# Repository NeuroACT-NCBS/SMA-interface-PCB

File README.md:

# SMA Interface PCB

KiCad PCB design for a reward-well controller for behavioral neuroscience experiments.

## Function

Built around an **RP2040-Zero** microcontroller. Takes 6 SMA coaxial sensor inputs from the spikegadgets ECU, through a schmitt-trigger buffer, and drives 4 TMC2209 stepper motors for reward dispensing. 8× AO3400A MOSFETs switch light and sounds. Two stacked USB-A ports allow to connect with the reward wells.

## Requirements

- [KiCad](https://www.kicad.org/) 10.0+

Clone with `--recurse-submodules` to pull the [NeuroACT-KiCad-libraries](https://github.com/NeuroACT-NCBS/NeuroACT-KiCad-libraries) automatically:

```bash
git clone --recurse-submodules https://github.com/NeuroACT-NCBS/SMA-interface-pcb.git
```

## KiCad Plugins

- **Fabrication Toolkit** — for generating production Gerber files
- **Round Tracks** — configured via `.round-tracks-config`

## License

CERN Open Hardware Licence Version 2 — see [LICENSE](LICENSE)

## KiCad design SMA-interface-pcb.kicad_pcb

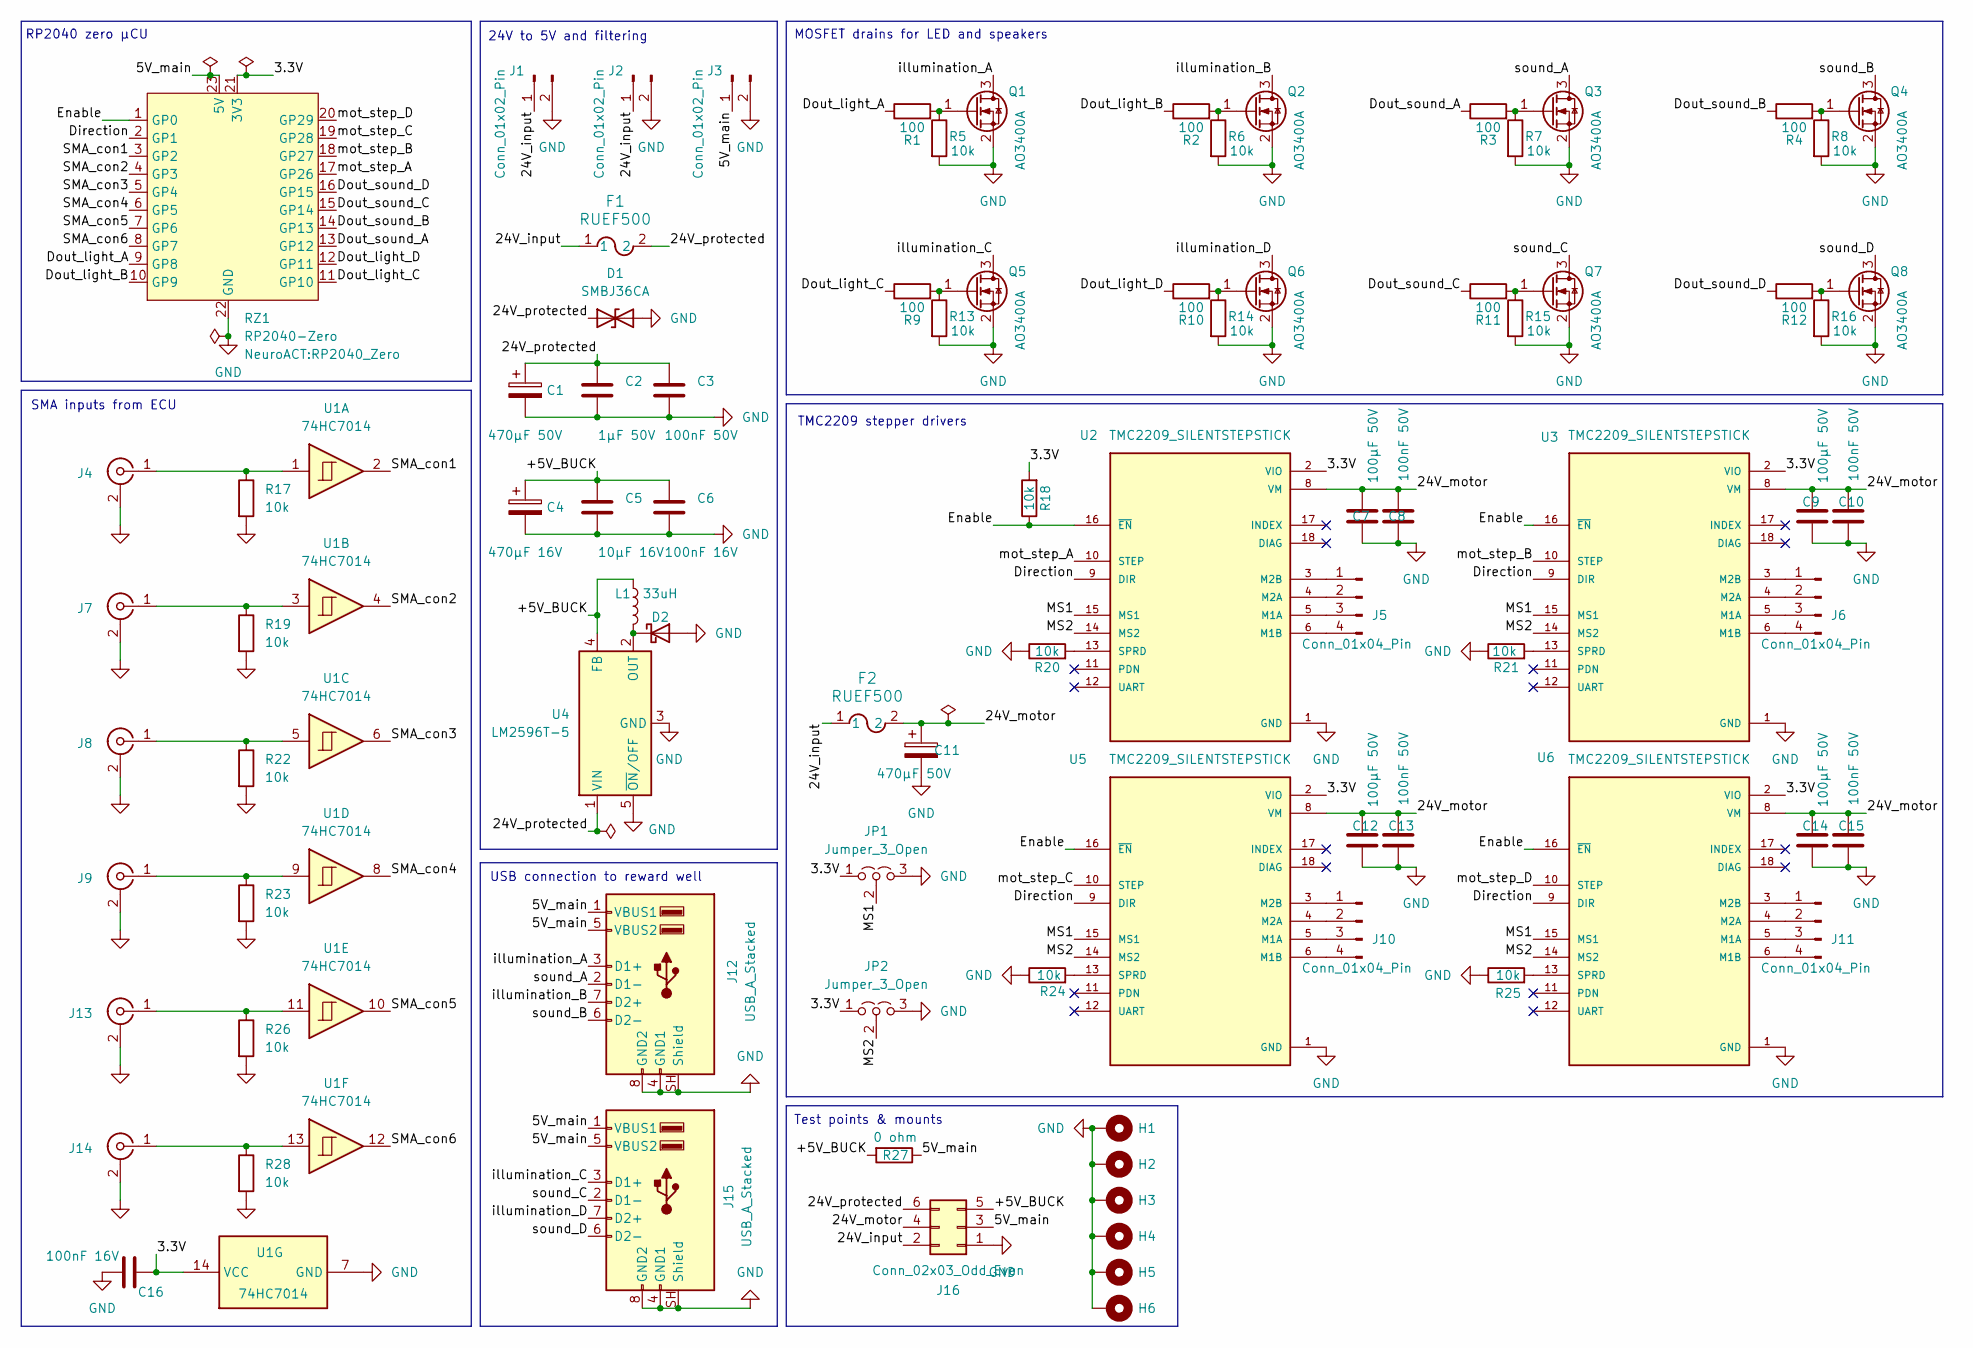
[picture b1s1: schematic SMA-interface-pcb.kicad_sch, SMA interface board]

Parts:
C1, C11: 470µF 50V; CP_Radial_D10.0mm_P5.00mm
C2: 1µF 50V; C_1206_3216Metric_Pad1.33x1.80mm_HandSolder
C3, C8, C10, C13, C15: 100nF 50V; C_1206_3216Metric_Pad1.33x1.80mm_HandSolder
C4: 470µF 16V; CP_Radial_D8.0mm_P5.00mm
C5: 10µF 16V; C_1206_3216Metric_Pad1.33x1.80mm_HandSolder
C6, C16: 100nF 16V; C_1206_3216Metric_Pad1.33x1.80mm_HandSolder
C7, C9, C12, C14: 100µF 50V; CP_Radial_horizontal_D8.0mm_P3.50mm
D1: SMBJ36CA; D_SMA-SMB_Universal_Handsoldering
D2: SR5100; D_DO-201AD_P15.24mm_Horizontal
F1, F2: RUEF500; FUSE_RUEF500_LTF
H1, H2, H3, H4, H5, H6: MountingHole; MountingHole_3.2mm_M3_DIN965_Pad_TopBottom
J1, J2, J3: Conn_01x02_Pin; Molex_Mini-Fit_Jr_5569-02A2_2x01_P4.20mm_Horizontal
J4, J7, J8, J9, J13, J14: Conn_Coaxial; SMA_Amphenol_901-143_Horizontal
J5, J6, J10, J11: Conn_01x04_Pin; PinHeader_1x04_P2.54mm_Vertical
J12, J15: USB_A_Stacked; USB_A_Wuerth_61400826021_Horizontal_Stacked
J16: Conn_02x03_Odd_Even; PinSocket_2x03_P2.54mm_Vertical
JP1, JP2: Jumper_3_Open; PinHeader_1x03_P2.54mm_Vertical
L1: 33uH; L_Toroid_Vertical_L16.0mm_W8.0mm_P7.62mm
Q1, Q2, Q3, Q4, Q5, Q6, Q7, Q8: AO3400A; SOT-23
R1, R2, R3, R4, R9, R10, R11, R12: 100; R_1206_3216Metric_Pad1.30x1.75mm_HandSolder
R5, R6, R7, R8, R13, R14, R15, R16, R17, R18, R19, R20, R21, R22, R23, R24, R25, R26, R28: 10k; R_1206_3216Metric_Pad1.30x1.75mm_HandSolder
R27: 0 ohm; R_1206_3216Metric_Pad1.30x1.75mm_HandSolder
RZ1: RP2040-Zero; RP2040_Zero
U1: 74HC7014; SOIC-14_3.9x8.7mm_P1.27mm
U2, U3, U5, U6: TMC2209_SILENTSTEPSTICK; MODULE_TMC2209_SILENTSTEPSTICK; PARTREV 1.20
U4: LM2596T-5; TO-220-5_Vertical

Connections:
/3.3V: C16.2, JP1.1 (A), JP2.1 (A), R18.2, RZ1.21 (3V3), U1.14 (VCC), U2.2 (VIO), U3.2 (VIO), U5.2 (VIO), U6.2 (VIO)
/5V_main: J3.1, J12.1 (VBUS1), J12.5 (VBUS2), J15.1 (VBUS1), J15.5 (VBUS2), J16.3, R27.1, RZ1.23 (5V)
/24V_input: F1.1, F2.1, J1.1, J2.1, J16.2
/24V_motor: C7.1, C8.1, C9.1, C10.1, C11.1, C12.1, C13.1, C14.1, C15.1, F2.2, J16.4, U2.8 (VM), U3.8 (VM), U5.8 (VM), U6.8 (VM)
/24V_protected: C1.1, C2.1, C3.1, D1.1 (A1), F1.2, J16.6, U4.1 (VIN)
/+5V_BUCK: C4.1, C5.1, C6.1, J16.5, L1.2, R27.2, U4.4 (FB)
/Direction: RZ1.2 (GP1), U2.9 (DIR), U3.9 (DIR), U5.9 (DIR), U6.9 (DIR)
/Dout_light_A: R1.1, RZ1.9 (GP8)
/Dout_light_B: R2.1, RZ1.10 (GP9)
/Dout_light_C: R9.1, RZ1.11 (GP10)
/Dout_light_D: R10.1, RZ1.12 (GP11)
/Dout_sound_A: R3.1, RZ1.13 (GP12)
/Dout_sound_B: R4.1, RZ1.14 (GP13)
/Dout_sound_C: R11.1, RZ1.15 (GP14)
/Dout_sound_D: R12.1, RZ1.16 (GP15)
/Enable: R18.1, RZ1.1 (GP0), U2.16 (~EN), U3.16 (~EN), U5.16 (~EN), U6.16 (~EN)
/MS1: JP1.2 (C), U2.15 (MS1), U3.15 (MS1), U5.15 (MS1), U6.15 (MS1)
/MS2: JP2.2 (C), U2.14 (MS2), U3.14 (MS2), U5.14 (MS2), U6.14 (MS2)
/SMA_con1: RZ1.3 (GP2), U1.2
/SMA_con2: RZ1.4 (GP3), U1.4
/SMA_con3: RZ1.5 (GP4), U1.6
/SMA_con4: RZ1.6 (GP5), U1.8
/SMA_con5: RZ1.7 (GP6), U1.10
/SMA_con6: RZ1.8 (GP7), U1.12
/illumination_A: J12.3 (D1+), Q1.3 (D)
/illumination_B: J12.7 (D2+), Q2.3 (D)
/illumination_C: J15.3 (D1+), Q5.3 (D)
/illumination_D: J15.7 (D2+), Q6.3 (D)
/mot_step_A: RZ1.17 (GP26), U2.10 (STEP)
/mot_step_B: RZ1.18 (GP27), U3.10 (STEP)
/mot_step_C: RZ1.19 (GP28), U5.10 (STEP)
/mot_step_D: RZ1.20 (GP29), U6.10 (STEP)
/sound_A: J12.2 (D1-), Q3.3 (D)
/sound_B: J12.6 (D2-), Q4.3 (D)
/sound_C: J15.2 (D1-), Q7.3 (D)
/sound_D: J15.6 (D2-), Q8.3 (D)
GND: C1.2, C2.2, C3.2, C4.2, C5.2, C6.2, C7.2, C8.2, C9.2, C10.2, C11.2, C12.2, C13.2, C14.2, C15.2, C16.1, D1.2 (A2), D2.2 (A), H1.1 (1_1), H2.1 (1_1), H3.1 (1_1), H4.1 (1_1), H5.1 (1_1), H6.1 (1_1), J1.2, J2.2, J3.2, J4.2 (Ext), J7.2 (Ext), J8.2 (Ext), J9.2 (Ext), J12.4 (GND1), J12.8 (GND2), J12.SH (Shield), J13.2 (Ext), J14.2 (Ext), J15.4 (GND1), J15.8 (GND2), J15.SH (Shield), J16.1, JP1.3 (B), JP2.3 (B), Q1.2 (S), Q2.2 (S), Q3.2 (S), Q4.2 (S), Q5.2 (S), Q6.2 (S), Q7.2 (S), Q8.2 (S), R5.2, R6.2, R7.2, R8.2, R13.2, R14.2, R15.2, R16.2, R17.2, R19.2, R20.1, R21.1, R22.2, R23.2, R24.1, R25.1, R26.2, R28.2, RZ1.22 (GND), U1.7 (GND), U2.1 (GND), U2.7 (GND), U3.1 (GND), U3.7 (GND), U4.3 (GND), U4.5 (~ON/OFF), U5.1 (GND), U5.7 (GND), U6.1 (GND), U6.7 (GND)
unnamed: D2.1 (K), L1.1, U4.2 (OUT)
unnamed: J4.1 (In), R17.1, U1.1
unnamed: J5.1, U2.3 (M2B)
unnamed: J5.2, U2.4 (M2A)
unnamed: J5.3, U2.5 (M1A)
unnamed: J5.4, U2.6 (M1B)
unnamed: J6.1, U3.3 (M2B)
unnamed: J6.2, U3.4 (M2A)
unnamed: J6.3, U3.5 (M1A)
unnamed: J6.4, U3.6 (M1B)
unnamed: J7.1 (In), R19.1, U1.3
unnamed: J8.1 (In), R22.1, U1.5
unnamed: J9.1 (In), R23.1, U1.9
unnamed: J10.1, U5.3 (M2B)
unnamed: J10.2, U5.4 (M2A)
unnamed: J10.3, U5.5 (M1A)
unnamed: J10.4, U5.6 (M1B)
unnamed: J11.1, U6.3 (M2B)
unnamed: J11.2, U6.4 (M2A)
unnamed: J11.3, U6.5 (M1A)
unnamed: J11.4, U6.6 (M1B)
unnamed: J13.1 (In), R26.1, U1.11
unnamed: J14.1 (In), R28.1, U1.13
unnamed: Q1.1 (G), R1.2, R5.1
unnamed: Q2.1 (G), R2.2, R6.1
unnamed: Q3.1 (G), R3.2, R7.1
unnamed: Q4.1 (G), R4.2, R8.1
unnamed: Q5.1 (G), R9.2, R13.1
unnamed: Q6.1 (G), R10.2, R14.1
unnamed: Q7.1 (G), R11.2, R15.1
unnamed: Q8.1 (G), R12.2, R16.1
unnamed: R20.2, U2.13 (SPRD)
unnamed: R21.2, U3.13 (SPRD)
unnamed: R24.2, U5.13 (SPRD)
unnamed: R25.2, U6.13 (SPRD)

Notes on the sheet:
MOSFET drains for LED and speakers
24V to 5V and filtering
SMA inputs from ECU
TMC2209 stepper drivers
USB connection to reward well
Test points & mounts
RP2040 zero µCU

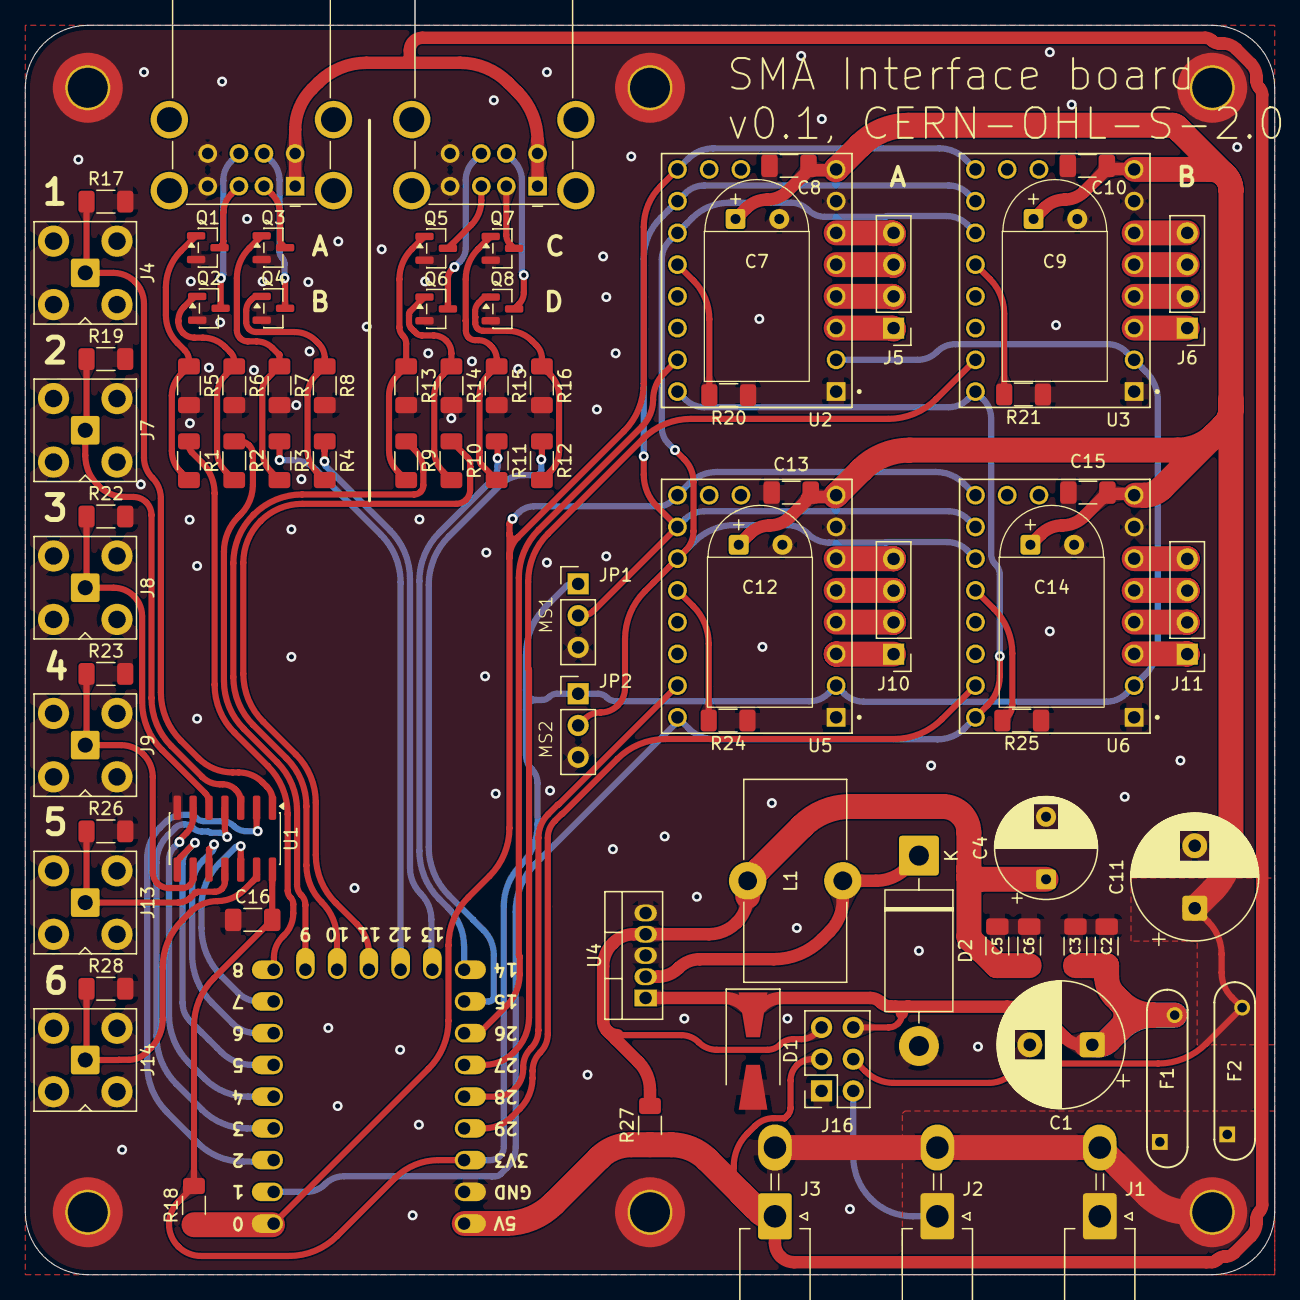
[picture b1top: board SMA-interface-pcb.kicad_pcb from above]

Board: 2 copper layers, 100.0 x 100.0 mm, 88 parts (0 on the bottom side), 72 nets.

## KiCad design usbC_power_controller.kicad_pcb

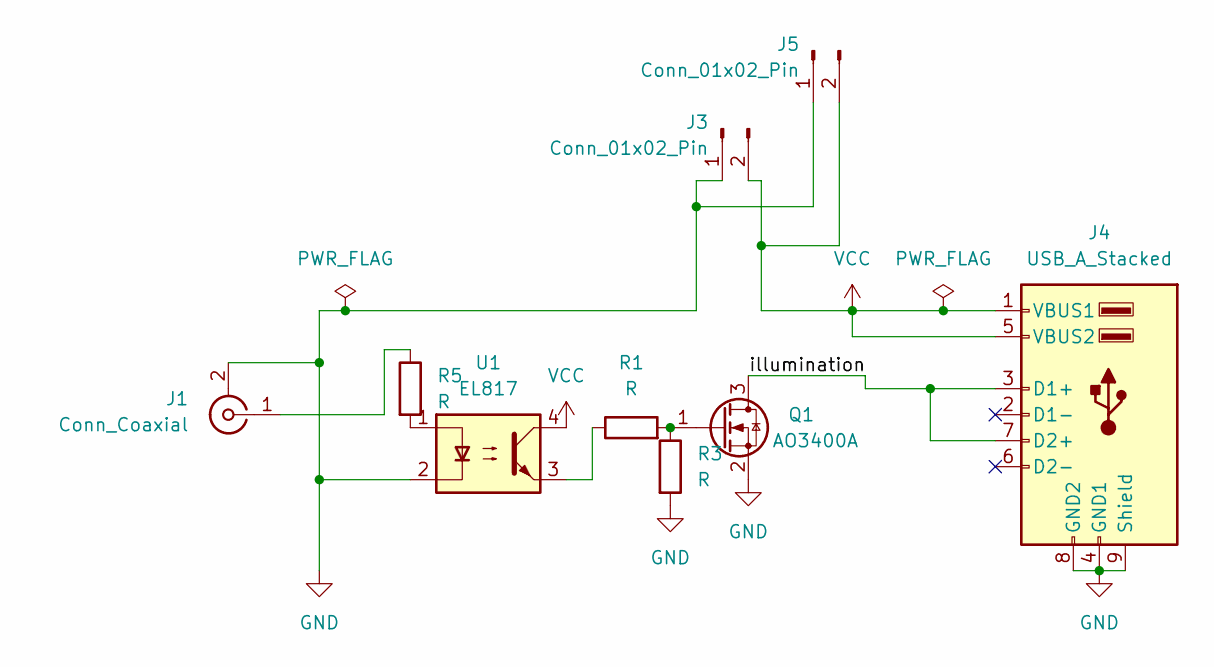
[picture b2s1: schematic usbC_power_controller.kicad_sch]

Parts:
J1: Conn_Coaxial; SMA_Molex_73251-2200_Horizontal
J3: Conn_01x02_Pin; Molex_Mini-Fit_Jr_5566-02A_2x01_P4.20mm_Vertical
J4: USB_A_Stacked; USB_A_Wuerth_61400826021_Horizontal_Stacked
J5: Conn_01x02_Pin; PinHeader_1x02_P2.54mm_Vertical
Q1: AO3400A; SOT-23
R1, R3, R5: R; R_Axial_DIN0204_L3.6mm_D1.6mm_P5.08mm_Horizontal
U1: EL817; DIP-4_W7.62mm_SMDSocket_SmallPads

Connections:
/illumination: J4.3 (D1+), J4.7 (D2+), Q1.3 (D)
GND: J1.2 (Ext), J3.1, J4.4 (GND1), J4.8 (GND2), J4.9 (Shield), J5.1, Q1.2 (S), R3.2, U1.2
unnamed: J1.1 (In), R5.1
unnamed: Q1.1 (G), R1.2, R3.1
unnamed: R1.1, U1.3
unnamed: R5.2, U1.1
VCC: J3.2, J4.1 (VBUS1), J4.5 (VBUS2), J5.2, U1.4

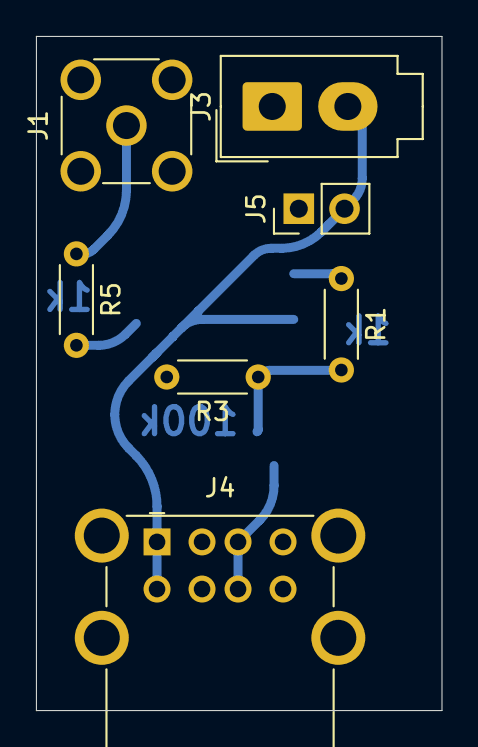
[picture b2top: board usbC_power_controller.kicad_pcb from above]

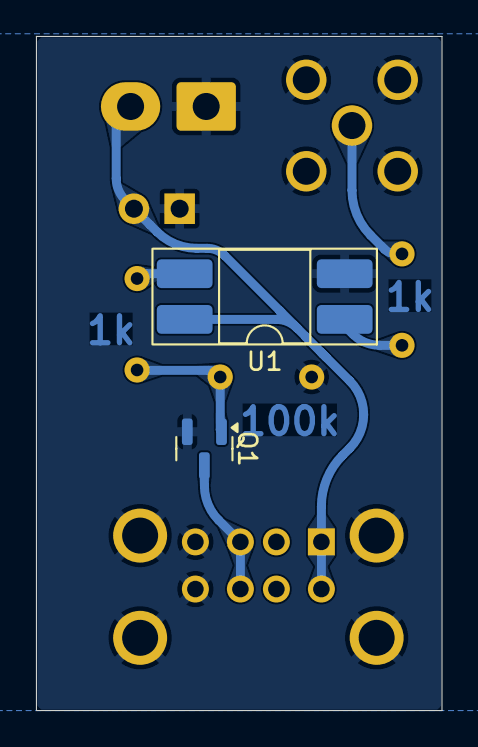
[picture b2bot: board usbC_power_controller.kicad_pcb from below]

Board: 2 copper layers, 22.5 x 37.5 mm, 9 parts (2 on the bottom side), 7 nets.

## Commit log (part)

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2025-06-25 Init project for SMA port of Behaviour arena PCBs
2025-12-10 first prototype of a working sma board
2025-12-11 updated power distribution board
2026-04-20 updated active buzzer system
2026-05-18 updated schematic to v0
2026-05-18 update Libraries submodule to latest
2026-05-19 Replace GNU GPL with CERN Open Hardware License
2026-05-20 added gitignore and updated submodule
2026-05-20 updated schematic with appropriate symbols, incomplete
2026-05-20 Readme updated
2026-05-27 updated schematic with appropriate symbols, to be verified
2026-05-30 first round of routing done
2026-06-04 footprint placement V1
2026-06-05 updated gitignore
2026-06-05 rounded tracks, updated Library

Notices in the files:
SMA-interface-pcb.kicad_pcb:
v0.1, CERN-OHL-S-2.0
